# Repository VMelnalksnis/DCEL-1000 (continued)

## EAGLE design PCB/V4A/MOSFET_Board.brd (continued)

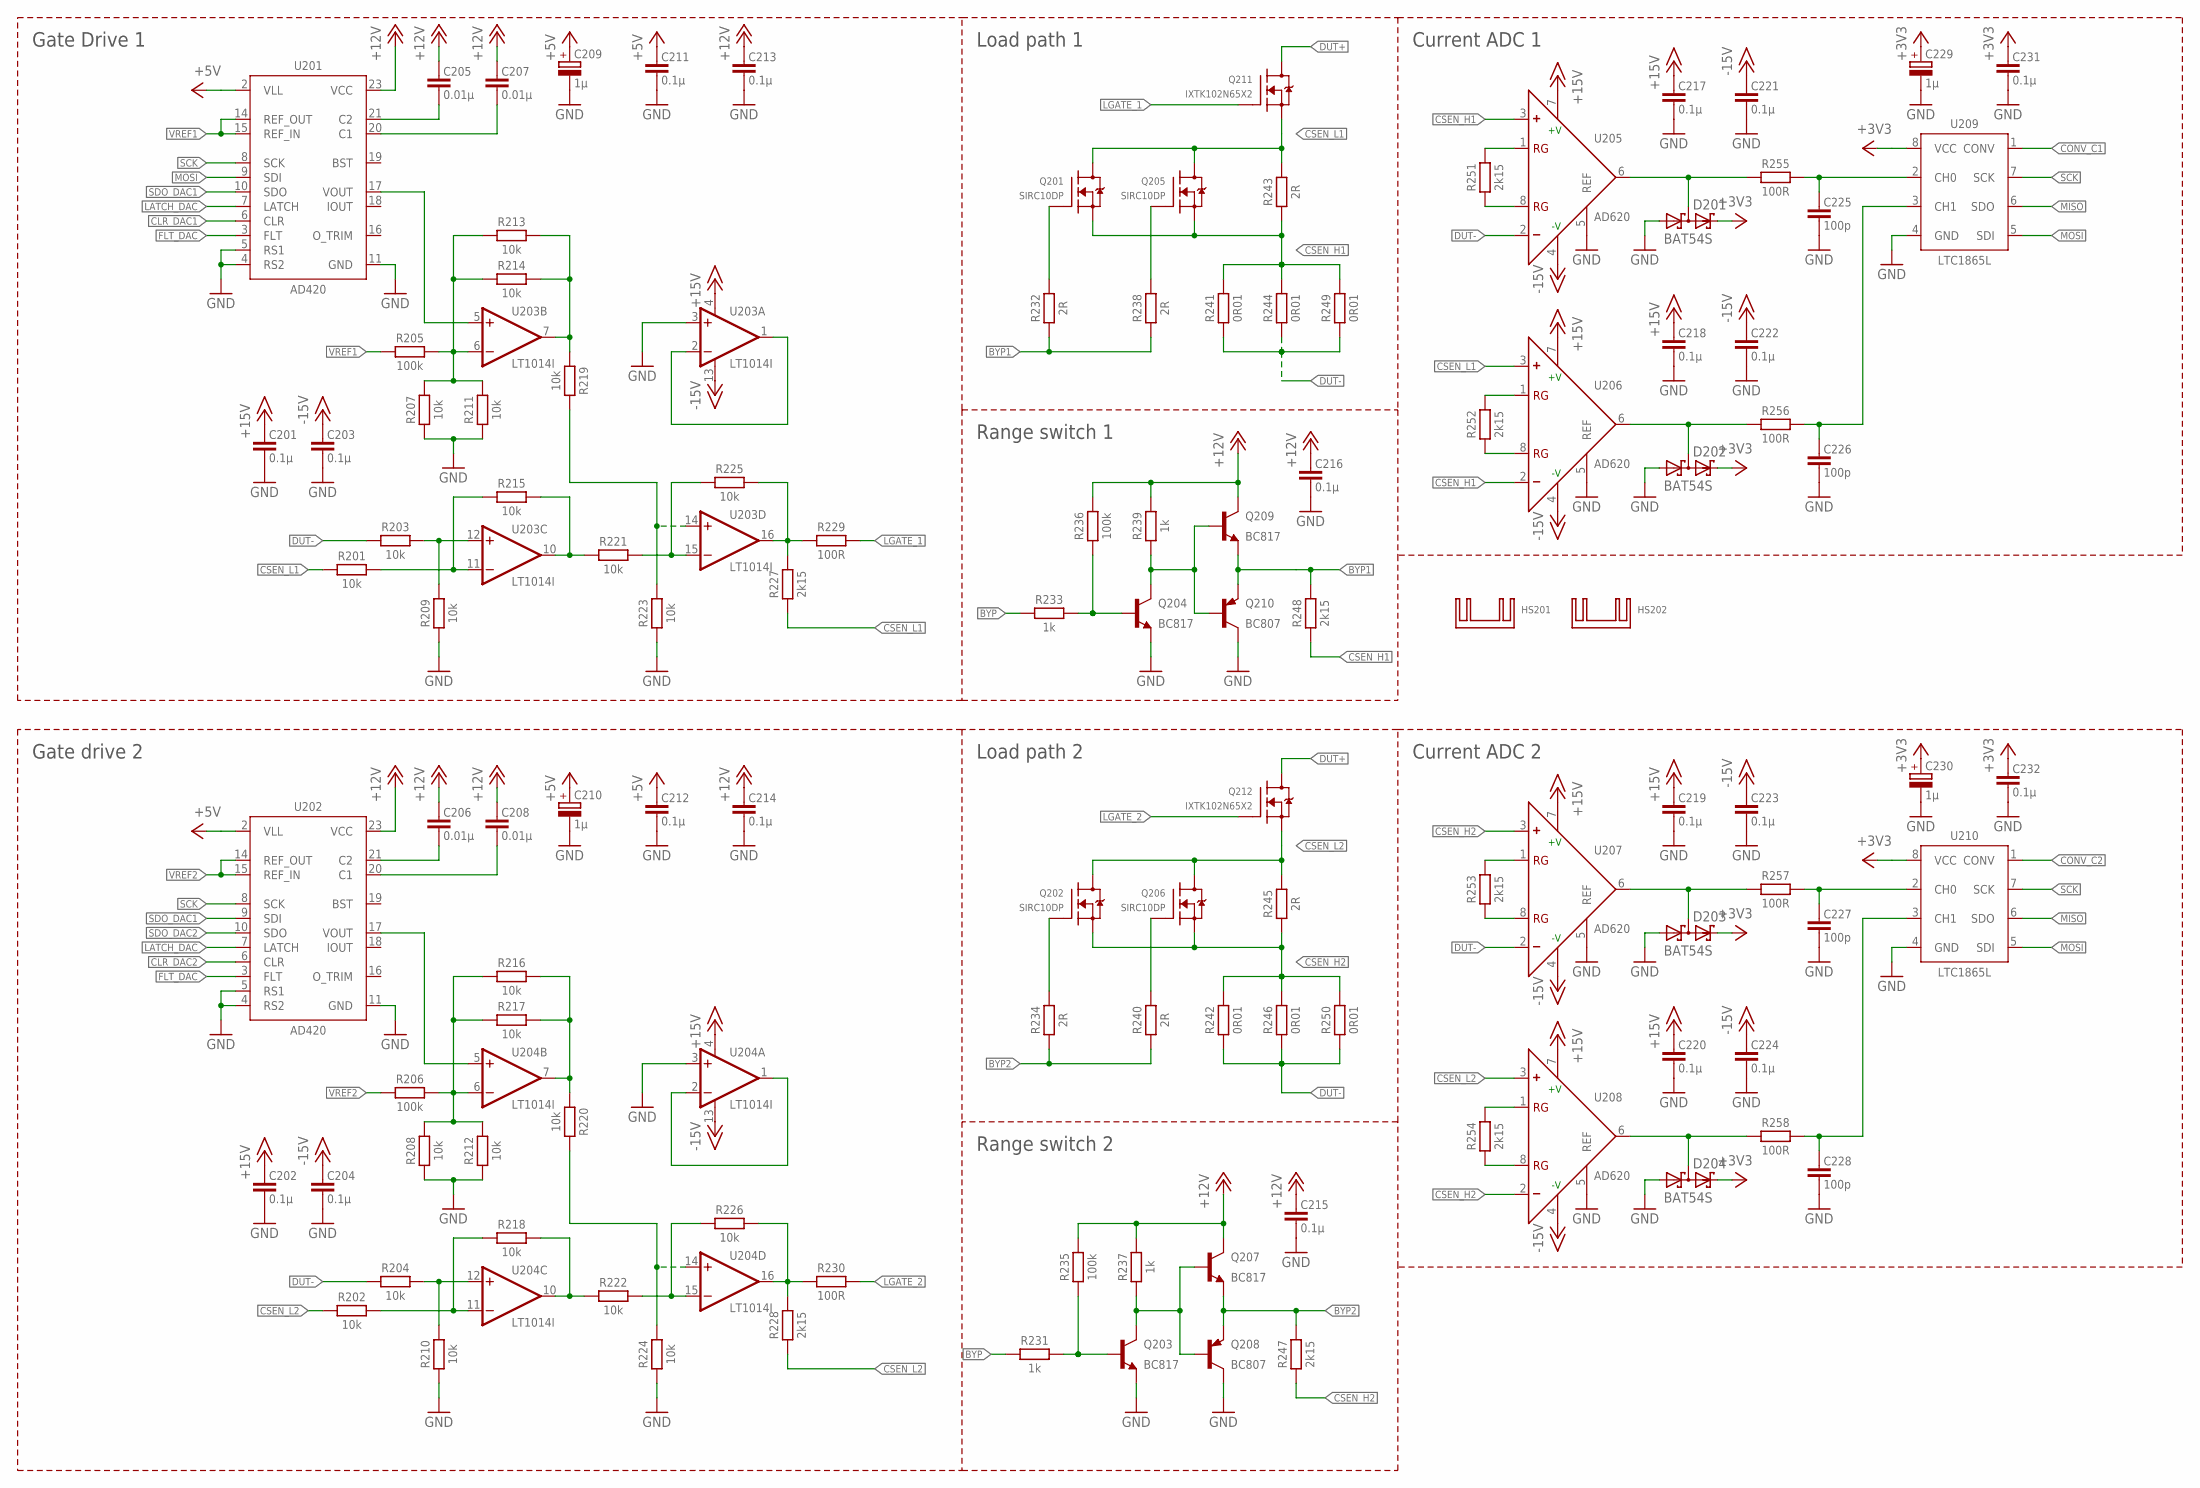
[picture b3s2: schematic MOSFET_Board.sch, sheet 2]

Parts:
C201, C202, C203, C204, C211, C212, C213, C214, C215, C216, C217, C218, C219, C220, C221, C222, C223, C224, C231, C232: 0.1µ; C1608
C205, C207: 0.01µ; C2012
C206, C208: 0.01µ; C3216
C209, C210, C229, C230: 1µ; CT3216
C225, C226, C227, C228: 100p; C1608
D201, D202, D203, D204: BAT54S; SOT23
HS201, HS202: HEATSINK-LGA115X
Q201, Q202, Q205, Q206: SIRC10DP; POWERPAK-SO-8
Q203, Q204, Q207, Q209: BC817; SOT23
Q208, Q210: BC807; SOT23
Q211, Q212: IXTK102N65X2; TO-264P-H-PADUP
R201, R202, R203, R204, R207, R208, R209, R210, R211, R212, R213, R214, R215, R216, R217, R218, R219, R220, R221, R222, R223, R224, R225, R226: 10k; R1608
R205, R206, R235, R236: 100k; R1608
R227, R228, R247, R248, R251, R252, R253, R254: 2k15; R2012W
R229, R230, R255, R256, R257, R258: 100R; R2012W
R231, R233, R237, R239: 1k; R1608
R232, R234, R238, R240, R243, R245: 2R; R3216W
R241, R242, R244, R246, R249, R250: 0R01; R6332W
U201, U202: AD420; SO24W
U203, U204: LT1014I; SO16W
U205, U206, U207, U208: AD620; SO8
U209, U210: LTC1865L; SO8

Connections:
+3V3: C229.+, C230.+, C231.1, C232.1, D201.2 (C2), D202.2 (C2), D203.2 (C2), D204.2 (C2), U209.8 (VCC), U210.8 (VCC); also elsewhere on the board
+5V: C209.+, C210.+, C211.1, C212.1, U201.2 (VLL), U202.2 (VLL); also elsewhere on the board
+12V: C205.1, C206.1, C207.1, C208.1, C213.1, C214.1, C215.1, C216.1, Q207.3 (C), Q209.3 (C), R235.2, R236.2, R237.2, R239.2, U201.23 (VCC), U202.23 (VCC); also elsewhere on the board
+15V: C201.1, C202.1, C217.1, C218.1, C219.1, C220.1, U203.4 (V+), U204.4 (V+), U205.7 (+V), U206.7 (+V), U207.7 (+V), U208.7 (+V); also elsewhere on the board
-15V: C203.1, C204.1, C221.1, C222.1, C223.1, C224.1, U203.13 (V-), U204.13 (V-), U205.4 (-V), U206.4 (-V), U207.4 (-V), U208.4 (-V); also elsewhere on the board
BPY1G1: Q201.4 (G), R232.2
BYP: R231.1, R233.1; also elsewhere on the board
BYP1: Q209.2 (E), Q210.2 (E), R232.1, R238.1, R248.1
BYP1G2: Q205.4 (G), R238.2
BYP2: Q207.2 (E), Q208.2 (E), R234.1, R240.1, R247.2
BYP2G1: Q202.4 (G), R234.2
BYP2G2: Q206.4 (G), R240.2
CLR_DAC1: U201.6 (CLR); also elsewhere on the board
CLR_DAC2: U202.6 (CLR); also elsewhere on the board
CONV_C1: U209.1 (CONV); also elsewhere on the board
CONV_C2: U210.1 (CONV); also elsewhere on the board
CSEN_H1: Q201.1 (S), Q201.2 (S), Q201.3 (S), Q205.1 (S), Q205.2 (S), Q205.3 (S), R241.2, R243.1, R244.2, R248.2, R249.2, U205.3 (+), U206.2 (-)
CSEN_H2: Q202.1 (S), Q202.2 (S), Q202.3 (S), Q206.1 (S), Q206.2 (S), Q206.3 (S), R242.2, R245.1, R246.2, R247.1, R250.2, U207.3 (+), U208.2 (-)
CSEN_L1: Q201.5 (D), Q205.5 (D), Q211.1 (S), R201.1, R227.1, R243.2, U206.3 (+)
CSEN_L2: Q202.5 (D), Q206.5 (D), Q212.1 (S), R202.1, R228.1, R245.2, U208.3 (+)
DAC_VOUT: U201.17 (VOUT), U203.5 (+IN)
DAC_VOUT1: U202.17 (VOUT), U204.5 (+IN)
DUT+: Q211.2 (D), Q212.2 (D); also elsewhere on the board
DUT-: R203.1, R204.1, R241.1, R242.1, R244.1, R246.1, R249.1, R250.1, U205.2 (-), U207.2 (-); also elsewhere on the board
FLT_DAC: U201.3 (FLT), U202.3 (FLT); also elsewhere on the board
GND: C201.2, C202.2, C203.2, C204.2, C209.-, C210.-, C211.2, C212.2, C213.2, C214.2, C215.2, C216.2, C217.2, C218.2, C219.2, C220.2, C221.2, C222.2, C223.2, C224.2, C225.2, C226.2, C227.2, C228.2, C229.-, C230.-, C231.2, C232.2, D201.1 (A1), D202.1 (A1), D203.1 (A1), D204.1 (A1), Q203.2 (E), Q204.2 (E), Q208.3 (C), Q210.3 (C), R207.1, R208.1, R209.1, R210.1, R211.1, R212.1, R223.1, R224.1, U201.4 (RS2), U201.5 (RS1), U201.11 (GND), U202.4 (RS2), U202.5 (RS1), U202.11 (GND), U203.3 (+IN), U204.3 (+IN), U205.5 (REF), U206.5 (REF), U207.5 (REF), U208.5 (REF), U209.4 (GND), U210.4 (GND); also elsewhere on the board
HIGHC1: C225.1, R255.2, U209.2 (CH0)
HIGHC2: C227.1, R257.2, U210.2 (CH0)
LATCH_DAC: U201.7 (LATCH), U202.7 (LATCH); also elsewhere on the board
LGATE_1: Q211.3 (G), R229.2
LGATE_2: Q212.3 (G), R230.2
LOWC1: C226.1, R256.2, U209.3 (CH1)
LOWC2: C228.1, R258.2, U210.3 (CH1)
MISO: U209.6 (SDO), U210.6 (SDO); also elsewhere on the board
MOSI: U201.9 (SDI), U209.5 (SDI), U210.5 (SDI); also elsewhere on the board
unnamed: R203.2, R209.2, U203.12 (+IN)
unnamed: R221.2, R225.1, U203.15 (-IN)
unnamed: C205.2, U201.21 (C2)
unnamed: C207.2, U201.20 (C1)
unnamed: Q204.3 (C), Q209.1 (B), Q210.1 (B), R239.1
unnamed: R225.2, R227.2, R229.1, U203.16 (OUT)
unnamed: D201.3 (C1A2), R255.1, U205.6 (OUT)
unnamed: Q204.1 (B), R233.2, R236.1
unnamed: R219.2, R223.2, U203.14 (+IN)
unnamed: R213.2, R214.2, R219.1, U203.7 (OUT)
unnamed: R205.2, R207.2, R211.2, R213.1, R214.1, U203.6 (-IN)
unnamed: R215.2, R221.1, U203.10 (OUT)
unnamed: R201.2, R215.1, U203.11 (-IN)
unnamed: U203.1 (OUT), U203.2 (-IN)
unnamed: D202.3 (C1A2), R256.1, U206.6 (OUT)
unnamed: Q203.3 (C), Q207.1 (B), Q208.1 (B), R237.1
unnamed: Q203.1 (B), R231.2, R235.1
unnamed: C206.2, U202.21 (C2)
unnamed: C208.2, U202.20 (C1)
unnamed: R206.2, R208.2, R212.2, R216.1, R217.1, U204.6 (-IN)
unnamed: R218.2, R222.1, U204.10 (OUT)
unnamed: R202.2, R218.1, U204.11 (-IN)
unnamed: R204.2, R210.2, U204.12 (+IN)
unnamed: R222.2, R226.1, U204.15 (-IN)
unnamed: R226.2, R228.2, R230.1, U204.16 (OUT)
unnamed: R220.2, R224.2, U204.14 (+IN)
unnamed: R216.2, R217.2, R220.1, U204.7 (OUT)
unnamed: U204.1 (OUT), U204.2 (-IN)
unnamed: D203.3 (C1A2), R257.1, U207.6 (OUT)
unnamed: D204.3 (C1A2), R258.1, U208.6 (OUT)
RG1_L1: R253.2, U207.1 (RG)
RG1_L2: R254.2, U208.1 (RG)
RG1_L3: R251.2, U205.1 (RG)
RG1_L4: R252.2, U206.1 (RG)
RG2_L1: R253.1, U207.8 (RG)
RG2_L2: R254.1, U208.8 (RG)
RG2_L3: R251.1, U205.8 (RG)
RG2_L4: R252.1, U206.8 (RG)
SCK: U201.8 (SCK), U202.8 (SCK), U209.7 (SCK), U210.7 (SCK); also elsewhere on the board
SDO_DAC1: U201.10 (SDO), U202.9 (SDI)
SDO_DAC2: U202.10 (SDO)
VREF1: R205.1, U201.14 (REF_OUT), U201.15 (REF_IN); also elsewhere on the board
VREF2: R206.1, U202.14 (REF_OUT), U202.15 (REF_IN)

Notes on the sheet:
Load path 1
Load path 2
Range switch 2
Range switch 1
Current ADC 1
Gate Drive 1
Gate drive 2
Current ADC 2

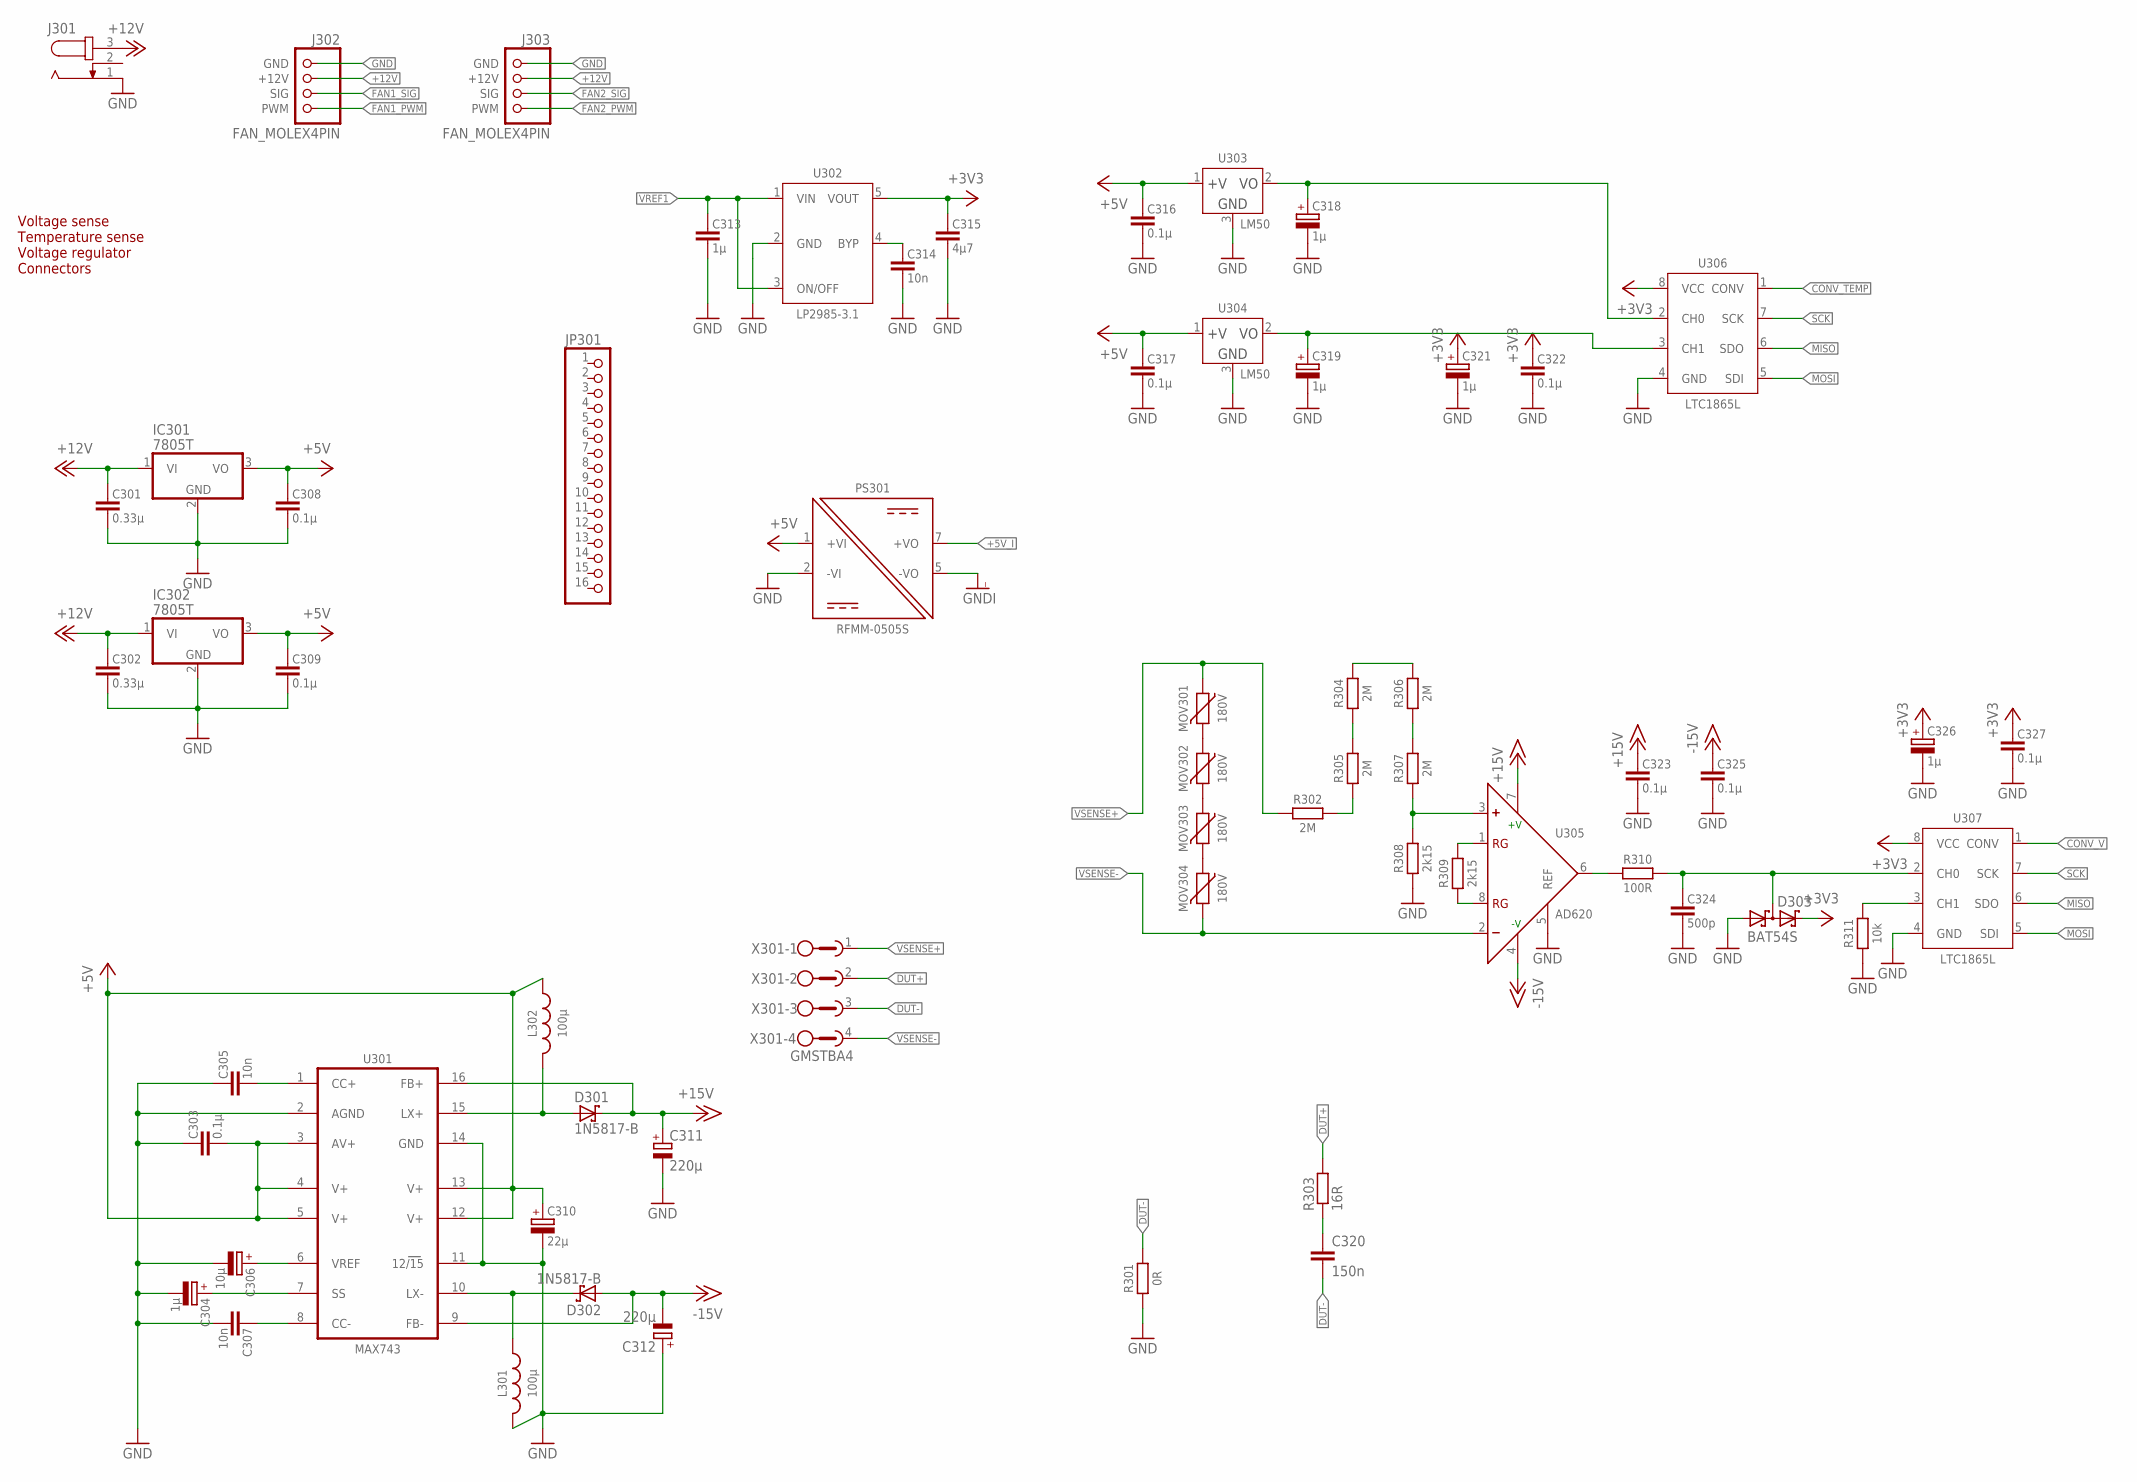
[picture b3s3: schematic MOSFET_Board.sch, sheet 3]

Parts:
C301, C302: 0.33µ; C3216
C303, C316, C317, C322, C323, C325, C327: 0.1µ; C3216
C304, C318, C319, C321, C326: 1µ; CT3216
C305, C307, C314: 10n; C2012
C306: 10µ; CT6032
C308, C309: 0.1µ; C1608
C310: 22µ; CT6032
C311, C312: 220µ; E3,5-10
C313: 1µ; C3216
C315: 4µ7; C3216
C320: 150n; C050-030X075
C324: 500p; C1608
D301, D302: 1N5817-B; DO41-7.6
D303: BAT54S; SOT23
IC301, IC302: 7805T; TO220H
J301: JACK-PLUG1; SPC4078
J302, J303: FAN_MOLEX4PIN; MOLEX_47053-1000
JP301: PINHD-1X16; 1X16
L301, L302: 100µ; MSS1260
MOV301, MOV302, MOV303, MOV304: 180V; R3225W
PS301: RFMM-0505S; RECOM-SIP7
R301: 0R; R3216W
R302, R304, R305, R306, R307: 2M; R3216W
R303: 16R; 0204/7
R308, R309: 2k15; R2012W
R310: 100R; R2012W
R311: 10k; R1608
U301: MAX743; SO16W
U302: LP2985-3.1; SOT23-5L
U303, U304: LM50; SOT23W
U305: AD620; SO8
U306, U307: LTC1865L; SO8
X301: GMSTBA4

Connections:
+3V3: C315.1, C321.+, C322.1, C326.+, C327.1, D303.2 (C2), U302.5 (VOUT), U306.8 (VCC), U307.8 (VCC); also elsewhere on the board
+5V: C303.2, C308.1, C309.1, C310.+, C316.1, C317.1, IC301.3 (VO), IC302.3 (VO), L302.1, PS301.1 (+VI), U301.3 (AV+), U301.4 (V+), U301.5 (V+), U301.12 (V+), U301.13 (V+), U303.1 (+V), U304.1 (+V); also elsewhere on the board
+5V_I: PS301.7 (+VO); also elsewhere on the board
+12V: C301.1, C302.1, IC301.1 (VI), IC302.1 (VI), J301.3, J302.2 (+12V), J303.2 (+12V); also elsewhere on the board
+15V: C311.+, C323.1, D301.C, U301.16 (FB+), U305.7 (+V); also elsewhere on the board
-15V: C312.-, C325.1, D302.A, U301.9 (FB-), U305.4 (-V); also elsewhere on the board
CONV_TEMP: U306.1 (CONV); also elsewhere on the board
CONV_V: U307.1 (CONV); also elsewhere on the board
DUT+: R303.2, X301.2; also elsewhere on the board
DUT-: C320.2, R301.2, X301.3; also elsewhere on the board
FAN1_PWM: J302.4 (PWM); also elsewhere on the board
FAN1_SIG: J302.3 (SIG)
FAN2_PWM: J303.4 (PWM); also elsewhere on the board
FAN2_SIG: J303.3 (SIG)
GND: C301.2, C302.2, C303.1, C304.-, C305.1, C306.-, C307.2, C308.2, C309.2, C310.-, C311.-, C312.+, C313.2, C314.2, C315.2, C316.2, C317.2, C318.-, C319.-, C321.-, C322.2, C323.2, C324.2, C325.2, C326.-, C327.2, D303.1 (A1), IC301.2 (GND), IC302.2 (GND), J301.1, J302.1 (GND), J303.1 (GND), L301.2, PS301.2 (-VI), R301.1, R308.1, R311.1, U301.2 (AGND), U301.11 (12/15), U301.14 (GND), U302.2 (GND), U303.3 (GND), U304.3 (GND), U305.5 (REF), U306.4 (GND), U307.4 (GND); also elsewhere on the board
GNDI: PS301.5 (-VO); also elsewhere on the board
MISO: U306.6 (SDO), U307.6 (SDO); also elsewhere on the board
MOSI: U306.5 (SDI), U307.5 (SDI); also elsewhere on the board
unnamed: C314.1, U302.4 (BYP)
unnamed: R310.1, U305.6 (OUT)
unnamed: R306.1, R307.2
unnamed: R304.2, R306.2
unnamed: R304.1, R305.2
unnamed: MOV301.2, MOV302.1
unnamed: R307.1, R308.2, U305.3 (+)
unnamed: C324.1, D303.3 (C1A2), R310.2, U307.2 (CH0)
unnamed: MOV302.2, MOV303.1
unnamed: R302.2, R305.1
unnamed: C307.1, U301.8 (CC-)
unnamed: C304.+, U301.7 (SS)
unnamed: MOV303.2, MOV304.1
unnamed: C305.2, U301.1 (CC+)
unnamed: D301.A, L302.2, U301.15 (LX+)
unnamed: D302.C, L301.1, U301.10 (LX-)
unnamed: R311.2, U307.3 (CH1)
unnamed: C320.1, R303.1
RG1_H6: R309.2, U305.1 (RG)
RG2_H6: R309.1, U305.8 (RG)
SCK: U306.7 (SCK), U307.7 (SCK); also elsewhere on the board
TEMP1: C318.+, U303.2 (VO), U306.2 (CH0)
TEMP2: C319.+, U304.2 (VO), U306.3 (CH1)
VREF1: C313.1, U302.1 (VIN), U302.3 (ON/OFF); also elsewhere on the board
VREF_MAX743: C306.+, U301.6 (VREF)
VSENSE+: MOV301.1, R302.1, X301.1
VSENSE-: MOV304.2, U305.2 (-), X301.4

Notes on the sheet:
Voltage sense Temperature sense Voltage regulator Connectors

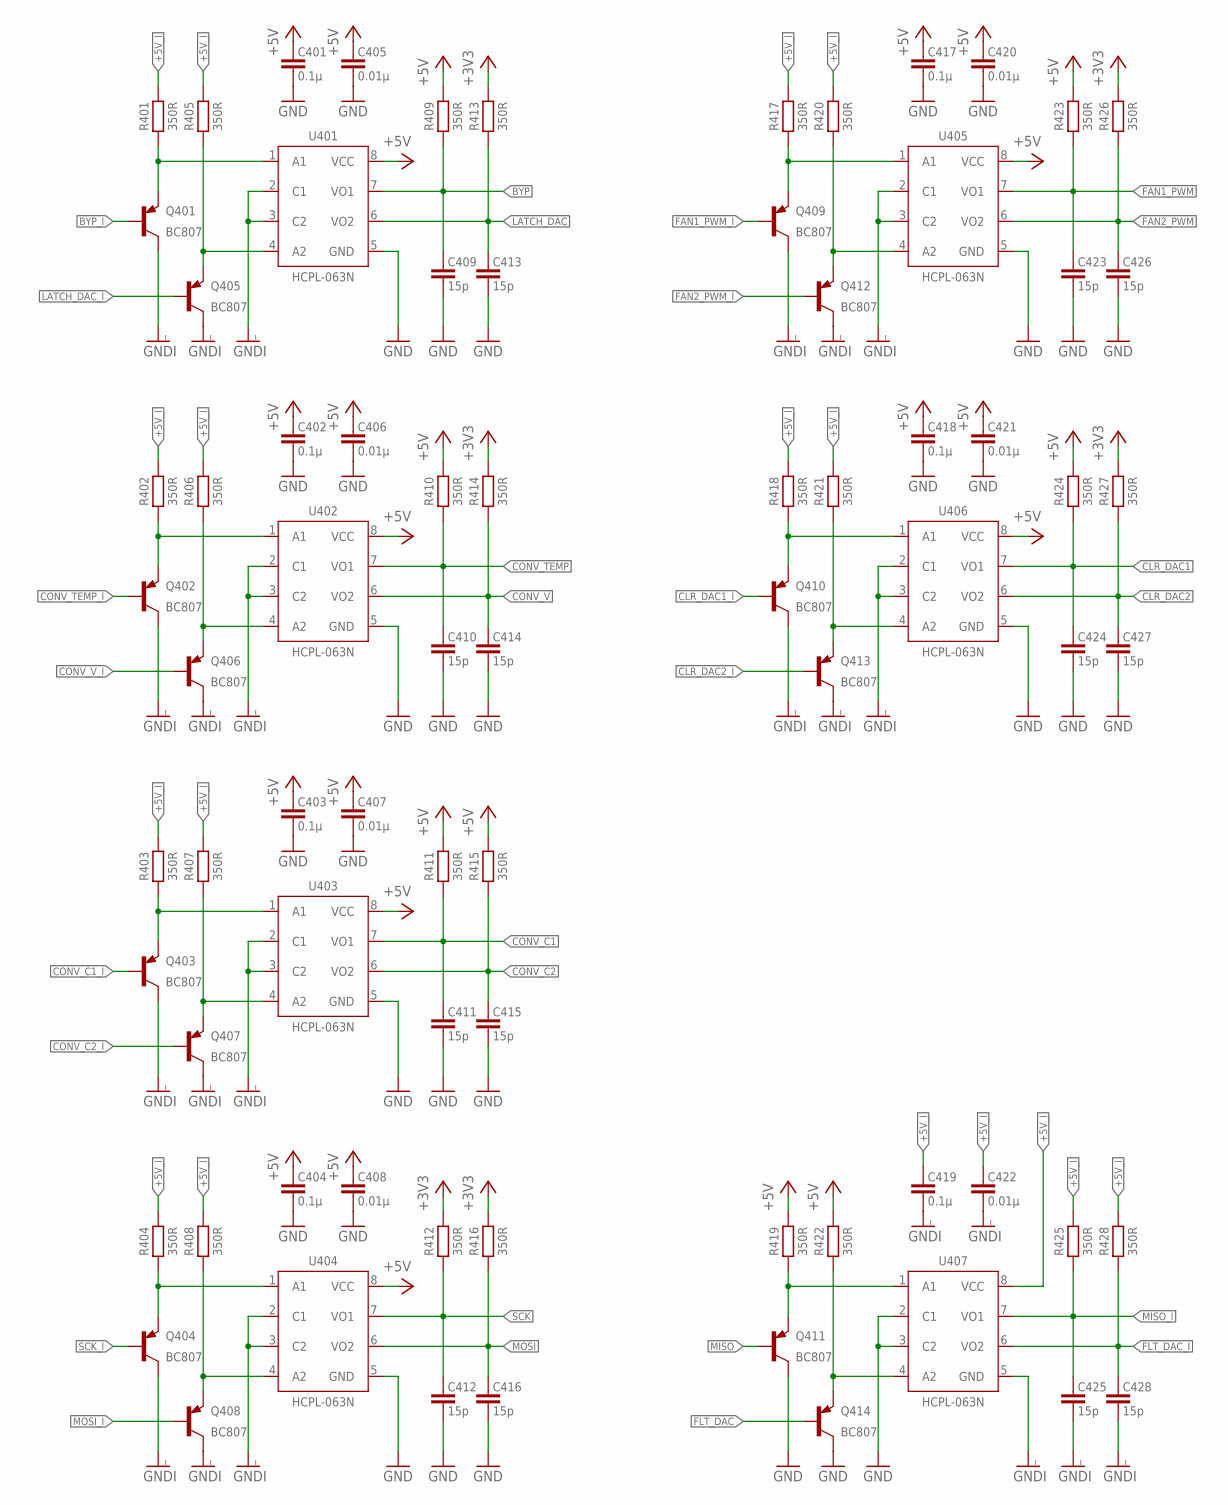
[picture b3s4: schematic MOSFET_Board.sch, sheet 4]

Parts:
C401, C402, C403, C404, C417, C418, C419: 0.1µ; C1608
C405, C406, C407, C408, C420, C421, C422: 0.01µ; C3216
C409, C410, C411, C412, C413, C414, C415, C416, C423, C424, C425, C426, C427, C428: 15p; C1608
Q401, Q402, Q403, Q404, Q405, Q406, Q407, Q408, Q409, Q410, Q411, Q412, Q413, Q414: BC807; SOT23
R401, R402, R403, R404, R405, R406, R407, R408, R409, R410, R411, R412, R413, R414, R415, R416, R417, R418, R419, R420, R421, R422, R423, R424, R425, R426, R427, R428: 350R; R1608
U401, U402, U403, U404, U405, U406, U407: HCPL-063N; SO8

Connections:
+3V3: R412.2, R413.2, R414.2, R416.2, R426.2, R427.2; also elsewhere on the board
+5V: C401.1, C402.1, C403.1, C404.1, C405.1, C406.1, C407.1, C408.1, C417.1, C418.1, C420.1, C421.1, R409.2, R410.2, R411.2, R415.2, R419.2, R422.2, R423.2, R424.2, U401.8 (VCC), U402.8 (VCC), U403.8 (VCC), U404.8 (VCC), U405.8 (VCC), U406.8 (VCC); also elsewhere on the board
+5V_I: C419.1, C422.1, R401.2, R402.2, R403.2, R404.2, R405.2, R406.2, R407.2, R408.2, R417.2, R418.2, R420.2, R421.2, R425.2, R428.2, U407.8 (VCC); also elsewhere on the board
BYP: C409.1, R409.1, U401.7 (VO1); also elsewhere on the board
BYP_I: Q401.1 (B)
CLR_DAC1: C424.1, R424.1, U406.7 (VO1); also elsewhere on the board
CLR_DAC1_I: Q410.1 (B)
CLR_DAC2: C427.1, R427.1, U406.6 (VO2); also elsewhere on the board
CLR_DAC2_I: Q413.1 (B)
CONV_C1: C411.1, R411.1, U403.7 (VO1); also elsewhere on the board
CONV_C1_I: Q403.1 (B)
CONV_C2: C415.1, R415.1, U403.6 (VO2); also elsewhere on the board
CONV_C2_I: Q407.1 (B)
CONV_TEMP: C410.1, R410.1, U402.7 (VO1); also elsewhere on the board
CONV_TEMP_I: Q402.1 (B)
CONV_V: C414.1, R414.1, U402.6 (VO2); also elsewhere on the board
CONV_V_I: Q406.1 (B)
FAN1_PWM: C423.1, R423.1, U405.7 (VO1); also elsewhere on the board
FAN1_PWM_I: Q409.1 (B)
FAN2_PWM: C426.1, R426.1, U405.6 (VO2); also elsewhere on the board
FAN2_PWM_I: Q412.1 (B)
FLT_DAC: Q414.1 (B); also elsewhere on the board
FLT_DAC_I: C428.1, R428.1, U407.6 (VO2)
GND: C401.2, C402.2, C403.2, C404.2, C405.2, C406.2, C407.2, C408.2, C409.2, C410.2, C411.2, C412.2, C413.2, C414.2, C415.2, C416.2, C417.2, C418.2, C420.2, C421.2, C423.2, C424.2, C426.2, C427.2, Q411.3 (C), Q414.3 (C), U401.5 (GND), U402.5 (GND), U403.5 (GND), U404.5 (GND), U405.5 (GND), U406.5 (GND), U407.2 (C1), U407.3 (C2); also elsewhere on the board
GNDI: C419.2, C422.2, C425.2, C428.2, Q401.3 (C), Q402.3 (C), Q403.3 (C), Q404.3 (C), Q405.3 (C), Q406.3 (C), Q407.3 (C), Q408.3 (C), Q409.3 (C), Q410.3 (C), Q412.3 (C), Q413.3 (C), U401.2 (C1), U401.3 (C2), U402.2 (C1), U402.3 (C2), U403.2 (C1), U403.3 (C2), U404.2 (C1), U404.3 (C2), U405.2 (C1), U405.3 (C2), U406.2 (C1), U406.3 (C2), U407.5 (GND); also elsewhere on the board
LATCH_DAC: C413.1, R413.1, U401.6 (VO2); also elsewhere on the board
LATCH_DAC_I: Q405.1 (B)
MISO: Q411.1 (B); also elsewhere on the board
MISO_I: C425.1, R425.1, U407.7 (VO1)
MOSI: C416.1, R416.1, U404.6 (VO2); also elsewhere on the board
MOSI_I: Q408.1 (B)
unnamed: Q411.2 (E), R419.1, U407.1 (A1)
unnamed: Q414.2 (E), R422.1, U407.4 (A2)
unnamed: Q404.2 (E), R404.1, U404.1 (A1)
unnamed: Q408.2 (E), R408.1, U404.4 (A2)
unnamed: Q402.2 (E), R402.1, U402.1 (A1)
unnamed: Q406.2 (E), R406.1, U402.4 (A2)
unnamed: Q409.2 (E), R417.1, U405.1 (A1)
unnamed: Q412.2 (E), R420.1, U405.4 (A2)
unnamed: Q401.2 (E), R401.1, U401.1 (A1)
unnamed: Q405.2 (E), R405.1, U401.4 (A2)
unnamed: Q410.2 (E), R418.1, U406.1 (A1)
unnamed: Q413.2 (E), R421.1, U406.4 (A2)
unnamed: Q403.2 (E), R403.1, U403.1 (A1)
unnamed: Q407.2 (E), R407.1, U403.4 (A2)
SCK: C412.1, R412.1, U404.7 (VO1); also elsewhere on the board
SCK_I: Q404.1 (B)

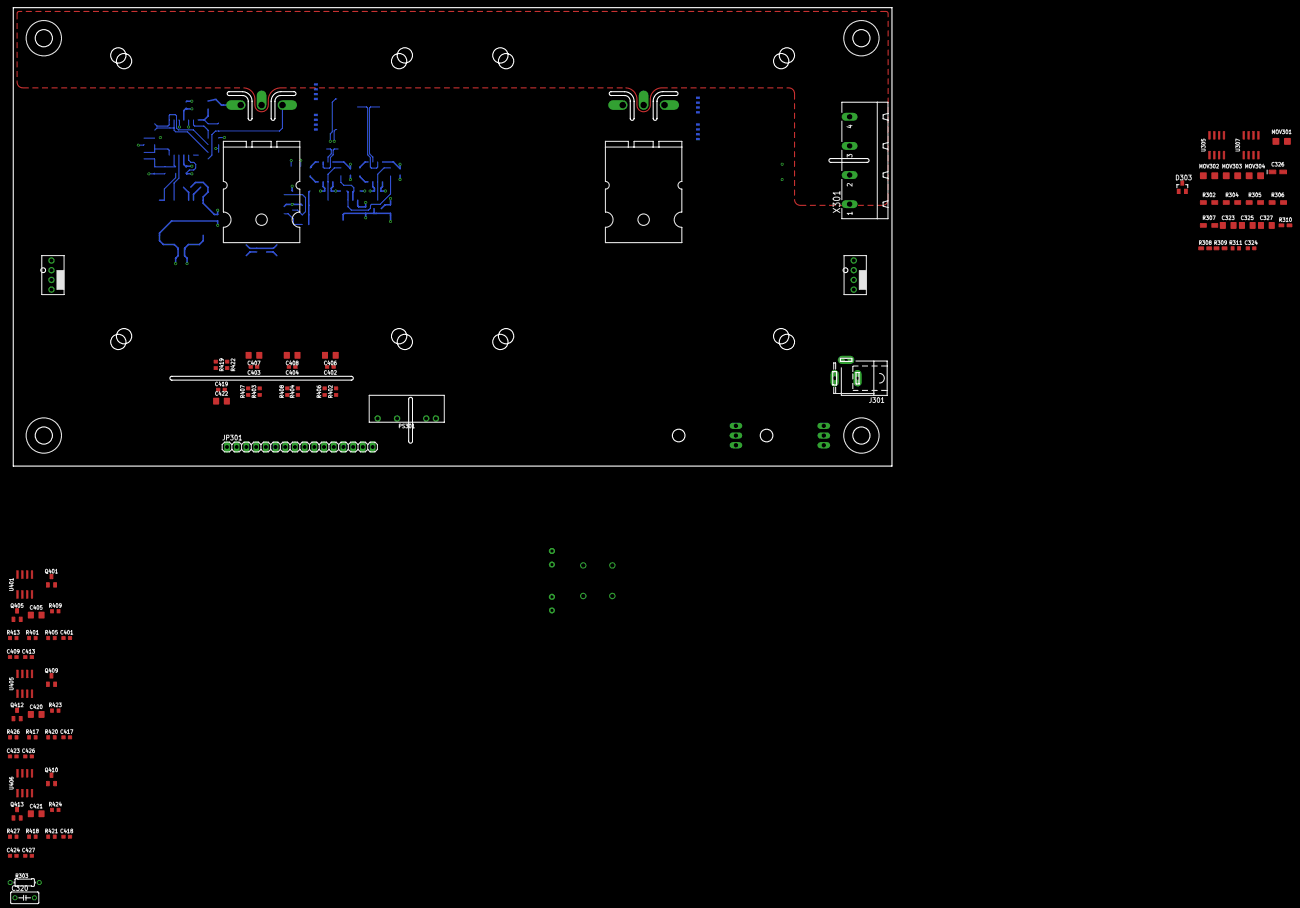
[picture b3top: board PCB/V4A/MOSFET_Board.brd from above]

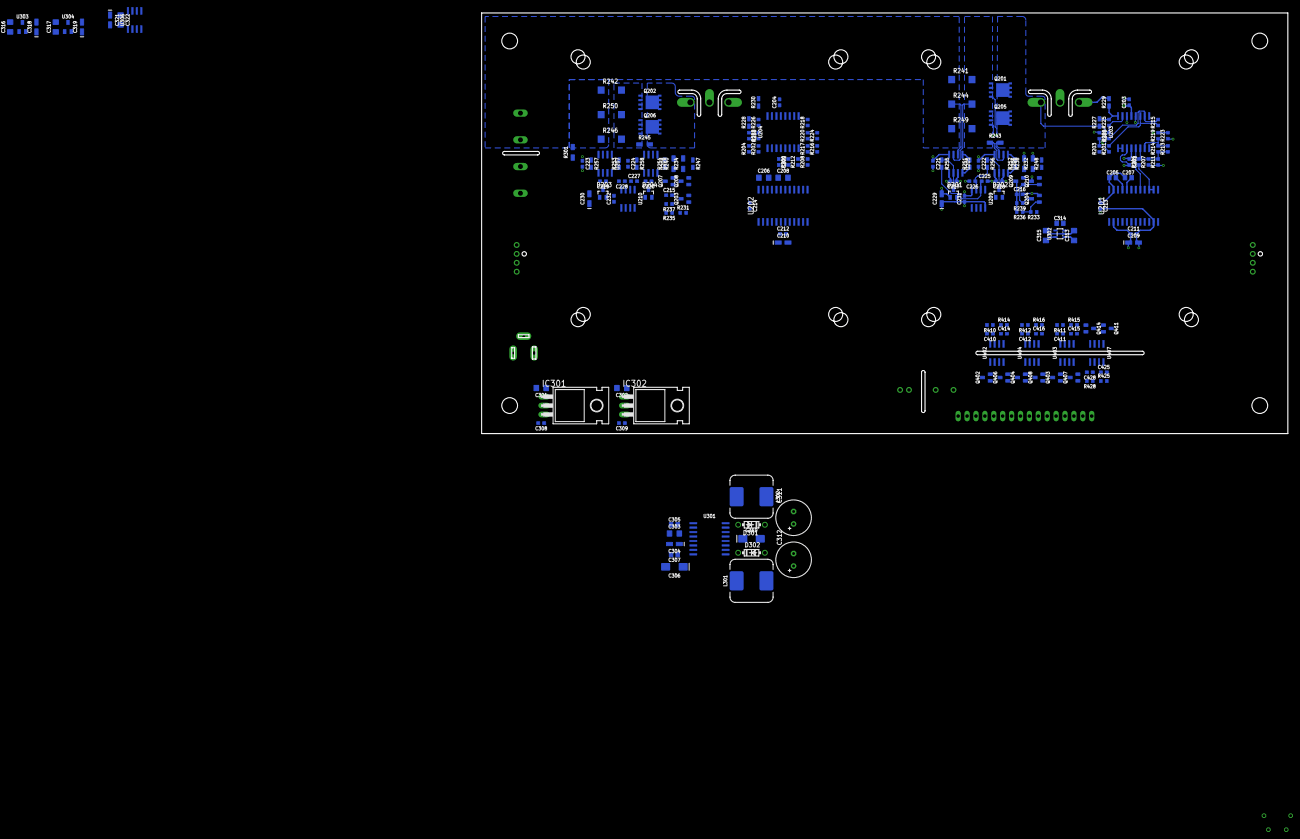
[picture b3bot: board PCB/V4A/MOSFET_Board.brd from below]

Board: 4 copper layers, 230.0 x 120.0 mm, 261 parts (175 on the bottom side), 124 nets.

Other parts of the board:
U$6, U$7, U$8, U$9: M4

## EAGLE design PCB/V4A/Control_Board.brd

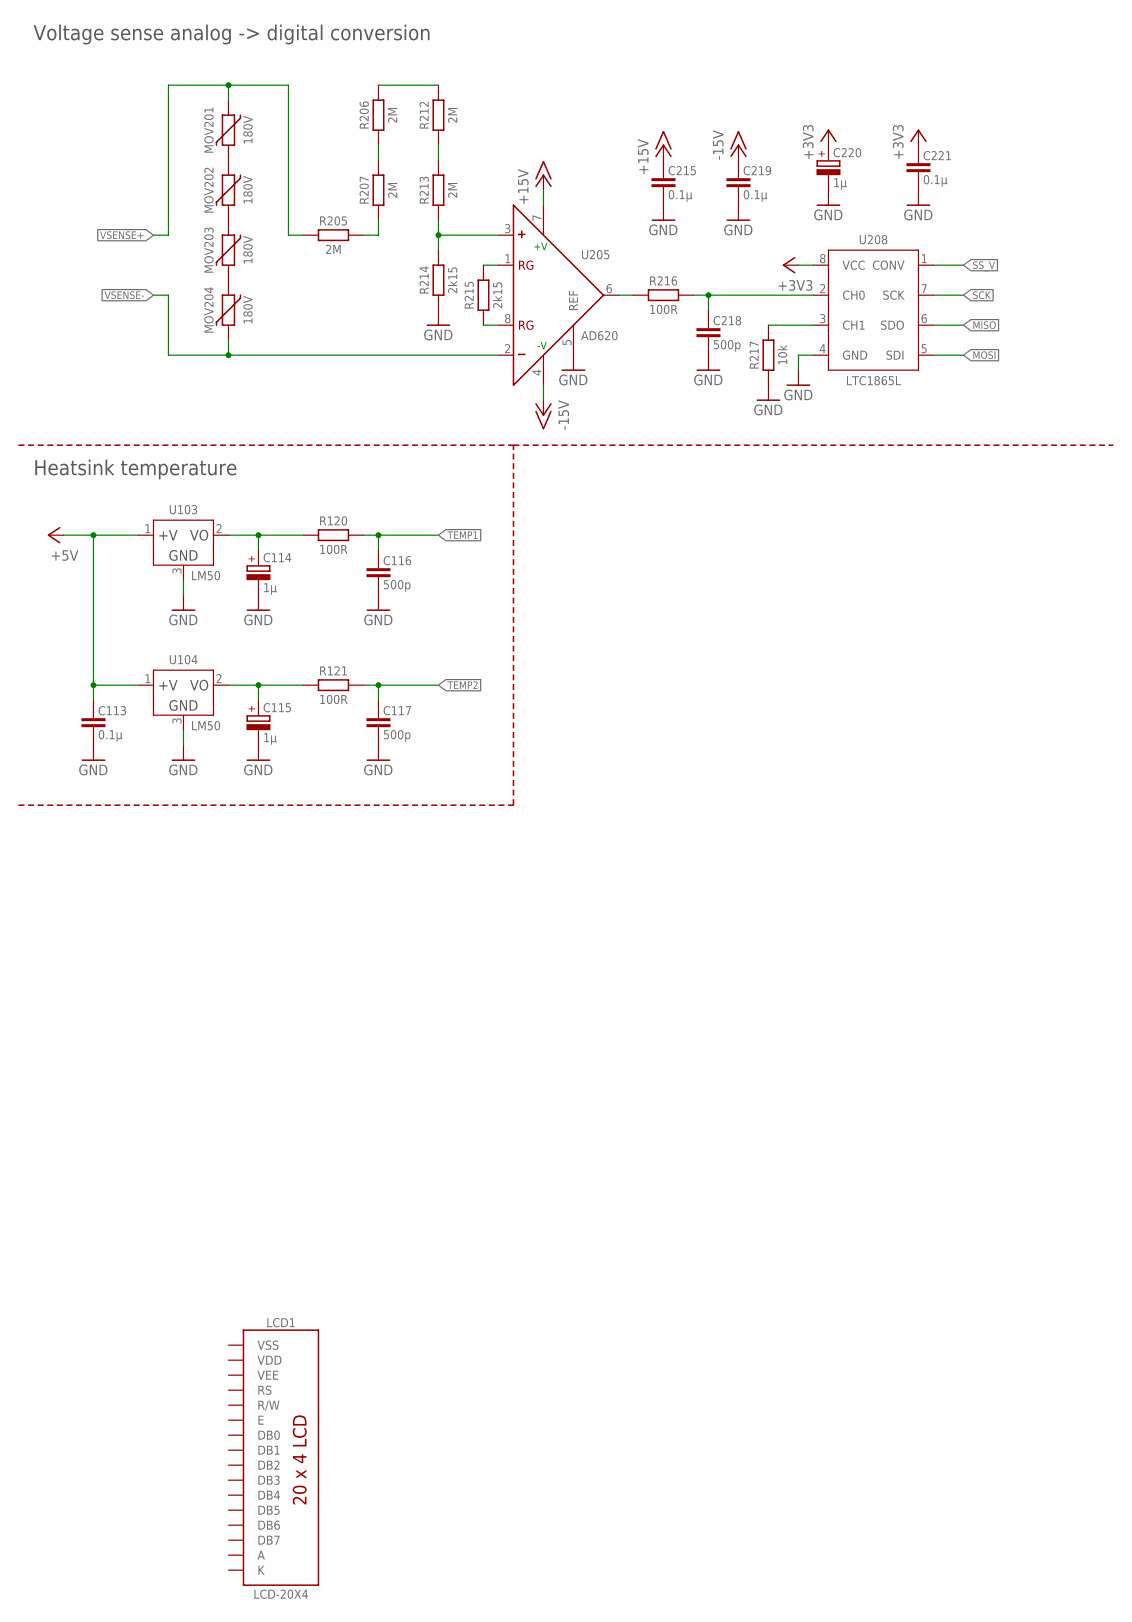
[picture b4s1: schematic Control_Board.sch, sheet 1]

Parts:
C113, C215, C219, C221: 0.1µ; C3216
C114, C115, C220: 1µ; CT3216
C116, C117, C218: 500p; C1608
LCD1: LCD-20X4; 4X20_LED
MOV201, MOV202, MOV203, MOV204: 180V; R3225W
R120, R121, R216: 100R; R2012W
R205, R206, R207, R212, R213: 2M; R3216W
R214, R215: 2k15; R2012W
R217: 10k; R1608
U103, U104: LM50; SOT23W
U205: AD620; SO8
U208: LTC1865L; SO8

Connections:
+3V3: C220.+, C221.1, U208.8 (VCC); also elsewhere on the board
+5V: C113.1, U103.1 (+V), U104.1 (+V); also elsewhere on the board
+15V: C215.1, U205.7 (+V); also elsewhere on the board
-15V: C219.1, U205.4 (-V); also elsewhere on the board
A: LCD1.15 (A)
GND: C113.2, C114.-, C115.-, C116.2, C117.2, C215.2, C218.2, C219.2, C220.-, C221.2, R214.1, R217.1, U103.3 (GND), U104.3 (GND), U205.5 (REF), U208.4 (GND); also elsewhere on the board
K: LCD1.16 (K)
MISO: U208.6 (SDO)
MOSI: U208.5 (SDI)
unnamed: MOV201.2, MOV202.1
unnamed: MOV202.2, MOV203.1
unnamed: R212.1, R213.2
unnamed: R206.2, R212.2
unnamed: R206.1, R207.2
unnamed: R205.2, R207.1
unnamed: R213.1, R214.2, U205.3 (+)
unnamed: C218.1, R216.2, U208.2 (CH0)
unnamed: R216.1, U205.6 (OUT)
unnamed: MOV203.2, MOV204.1
unnamed: R217.2, U208.3 (CH1)
RG1_H6: R215.2, U205.1 (RG)
RG2_H6: R215.1, U205.8 (RG)
SCK: U208.7 (SCK)
SS_V: U208.1 (CONV)
T1_OUT: C114.+, R120.1, U103.2 (VO)
T2_OUT: C115.+, R121.1, U104.2 (VO)
TEMP1: C116.1, R120.2
TEMP2: C117.1, R121.2
VDD: LCD1.2 (VDD)
VEE: LCD1.3 (VEE)
VSENSE+: MOV201.1, R205.1
VSENSE-: MOV204.2, U205.2 (-)
VSS: LCD1.1 (VSS)

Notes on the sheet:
Voltage sense analog -> digital conversion
Heatsink temperature
